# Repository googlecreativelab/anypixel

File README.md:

[AnyPixel.js](http://googlecreativelab.github.io/anypixel) is an open-source software and hardware library that makes it possible to use the web to create big, unusual, interactive displays. Anyone can fork the code and the schematics to create their own display at any scale.

The first display using this platform is in the 8th Avenue lobby at the Google NYC office. To create this installation, we used 5880 off-the-shelf arcade buttons with LEDs inside them as our pixels. AnyPixel.js’ straightforward hardware/software framework makes it easy to build any display where each pixel is an interactive element.

## What You'll Find
- **/hardware** - EAGLE schematics, board layouts, CAD files, wiring diagrams, and blueprints.
- **/firmware** - microcontroller code, written for the STM32 family of devices.
- **/backend** - node.js and chrome applications for communicating with the hardware.
- **/frontend** - the app framework, an in-browser previewer, and 12 example apps written by Googlers and friends worldwide.
- **/rpi-example** - a simple starter example connecting a Raspberry Pi with AnyPixel to a single button for round trip communication.

## Getting Started

### Check out the examples 
We've included 12 example apps written by Googlers and friends for the 8th Avenue lobby display in NYC. To check them out, install the [previewer](https://github.com/googlecreativelab/anypixel/tree/master/frontend/previewer) and run one of the [examples](https://github.com/googlecreativelab/anypixel/tree/master/frontend/examples).

### Build your own app 
Building your own app is easy with the Anypixel framework. To get started, check out the [framework documentation](https://github.com/googlecreativelab/anypixel/tree/master/frontend/framework) and the [example app](https://github.com/googlecreativelab/anypixel/tree/master/frontend/examples/getting-started):

```js
var anypixel = require('anypixel'); 
var ctx = anypixel.canvas.getContext2D();

var colors = ['#F00', '#0F0', '#00F'];

/**  
 * Listen for onButtonDown events and draw a 2x2 rectangle at the event site
 */
document.addEventListener('onButtonDown', function(event) {   
	ctx.fillStyle = colors[Math.floor(Math.random() * colors.length)];
	ctx.fillRect(event.detail.x - 1, event.detail.y - 1, 2, 2);
}); 
```

## Contributors
- [Jeremy Abel](https://github.com/jeremyabel)
- [Kyle Phillips](https://github.com/hapticdata)
- [Nick Fox-Gieg](https://github.com/n1ckfg)
- [Jeramy Morrill](https://github.com/theceremony)
- [Manny Tan](https://github.com/mannytan)
- [Felix Woitzel](https://github.com/flexi23)
- [Anders Hoff](https://github.com/inconvergent)
- [Dimitry Bentsionov](https://github.com/dimitry)
- [Nick Stahlnecker](https://github.com/Stahlneckr)
- [Nick Jonas](https://github.com/nick-jonas)
- [Patrick Miller](https://github.com/patrickdmiller)

## Note
Third party directories may have different (non-Apache 2.0) licenses.

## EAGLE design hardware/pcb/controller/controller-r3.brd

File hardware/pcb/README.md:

# Electronics Overview

## Power

24v power is delivered from the power supply boxes to the LED boards through a 4A fuse. On each LED
board the 24v rail powers three identical 5v buck converters (or alternatively a single 1/4 brick
supply with the three 5v rails bridged together) which provide power to the LEDs and is further
stepped down to 3.3v to power the microcontrollers.  There is also a power supply that steps the 24v
down to 12v to power the cooling fan. The 24v rail is also connected to the RJ12 connection which
goes to the IP controller.

The IP controller has a diode ORing arrangement, accepting power from any of the 4 LED boards and/or
an additional external supply via a barrel connector. There are two switching supplies on the IP
controller board, one with a 3.3v output to power all the onboard electronics, and a 5v output
device for powering accessories through a 2 pin header.

## Data Flow

The IP controller board contains a 3 port 100Mbit Ethernet switch with two ports exposed as RJ45
connectors which allows for daisy chaining boards together eliminating the need for long cable runs
back to a single large switch. The third port of this switch is connected to the STM32F407
microcontroller on the IP controller which takes in packets containing data for a complete 14x14
button panel. The firmware divides this data into 4 smaller packets and send these to the 4
connected 7x7 LED boards.

Communication to the LED boards is over asynchronous serial with a baud rate of 1Mbit.  There are 5
STM32F030 microcontrollers on each LED board that each control 9 or 10 RGB LEDs and have the same
number of thermistors and switches as input.  The thermistors are used to report the temperature of
each LED, and the switch is used for user input. The microcontrollers are connected in a chain, with
the TX from the IP controller connected to the first microcontroller's RX, and then the first
microcontroller's TX to the second microcontroller's RX and so on until the 5th microcontroller's TX
connects back to the IP controller's RX.  This configuration and the firmware make the LED board
behave like a large shift register, with each processor gathering its input and replacing it with
its output in the appropriate location in each packet based on its address as the stream of data is
shifted through it.  The packets are delimited by an idle state on the serial line (no signal edges
occur in the time it takes to transmit a complete byte, or about 10 microseconds).

The interface from the STM32F030 microcontrollers to the two TLC59401 LED drivers it controls is
like a shift register as well.  The two TLC59401 chips are connected in series.  There are
additional connections to the TLC59401 to facilitate the PWM signal generation, these include a
grayscale clock and a blanking signal.

## LED drive

The TLC59401 chip is a 16 channel constant current supply PWM controlled LED driver.  The device has
a global reference resistor to set the maximum channel current.  Each channel then has an analog dot
correct circuit which controls the current reference in 64 steps.  This dot correction feature is
used for rough calibration and is not changed during operation.  The global reference combined with
the dot correction circuit provide for a constant current output to drive the LEDs.

The TLC59401 also has PWM to toggle the constant current outputs on and off with a programmable duty
cycle. This is a 12-bit PWM system yielding 4096 discrete intensities for the output on top of the
5-bit/64 value dot correction values, which provides a 17-bit range for the system.  The firmware
implements a lookup table for converting from the typical 8-bits per channel input media to the
12-bit PWM values. Due to memory constrains the lookup table has only 65 entries and uses linear
interpolation to map the complete 256-value/8-bit input range to appropriate output values.

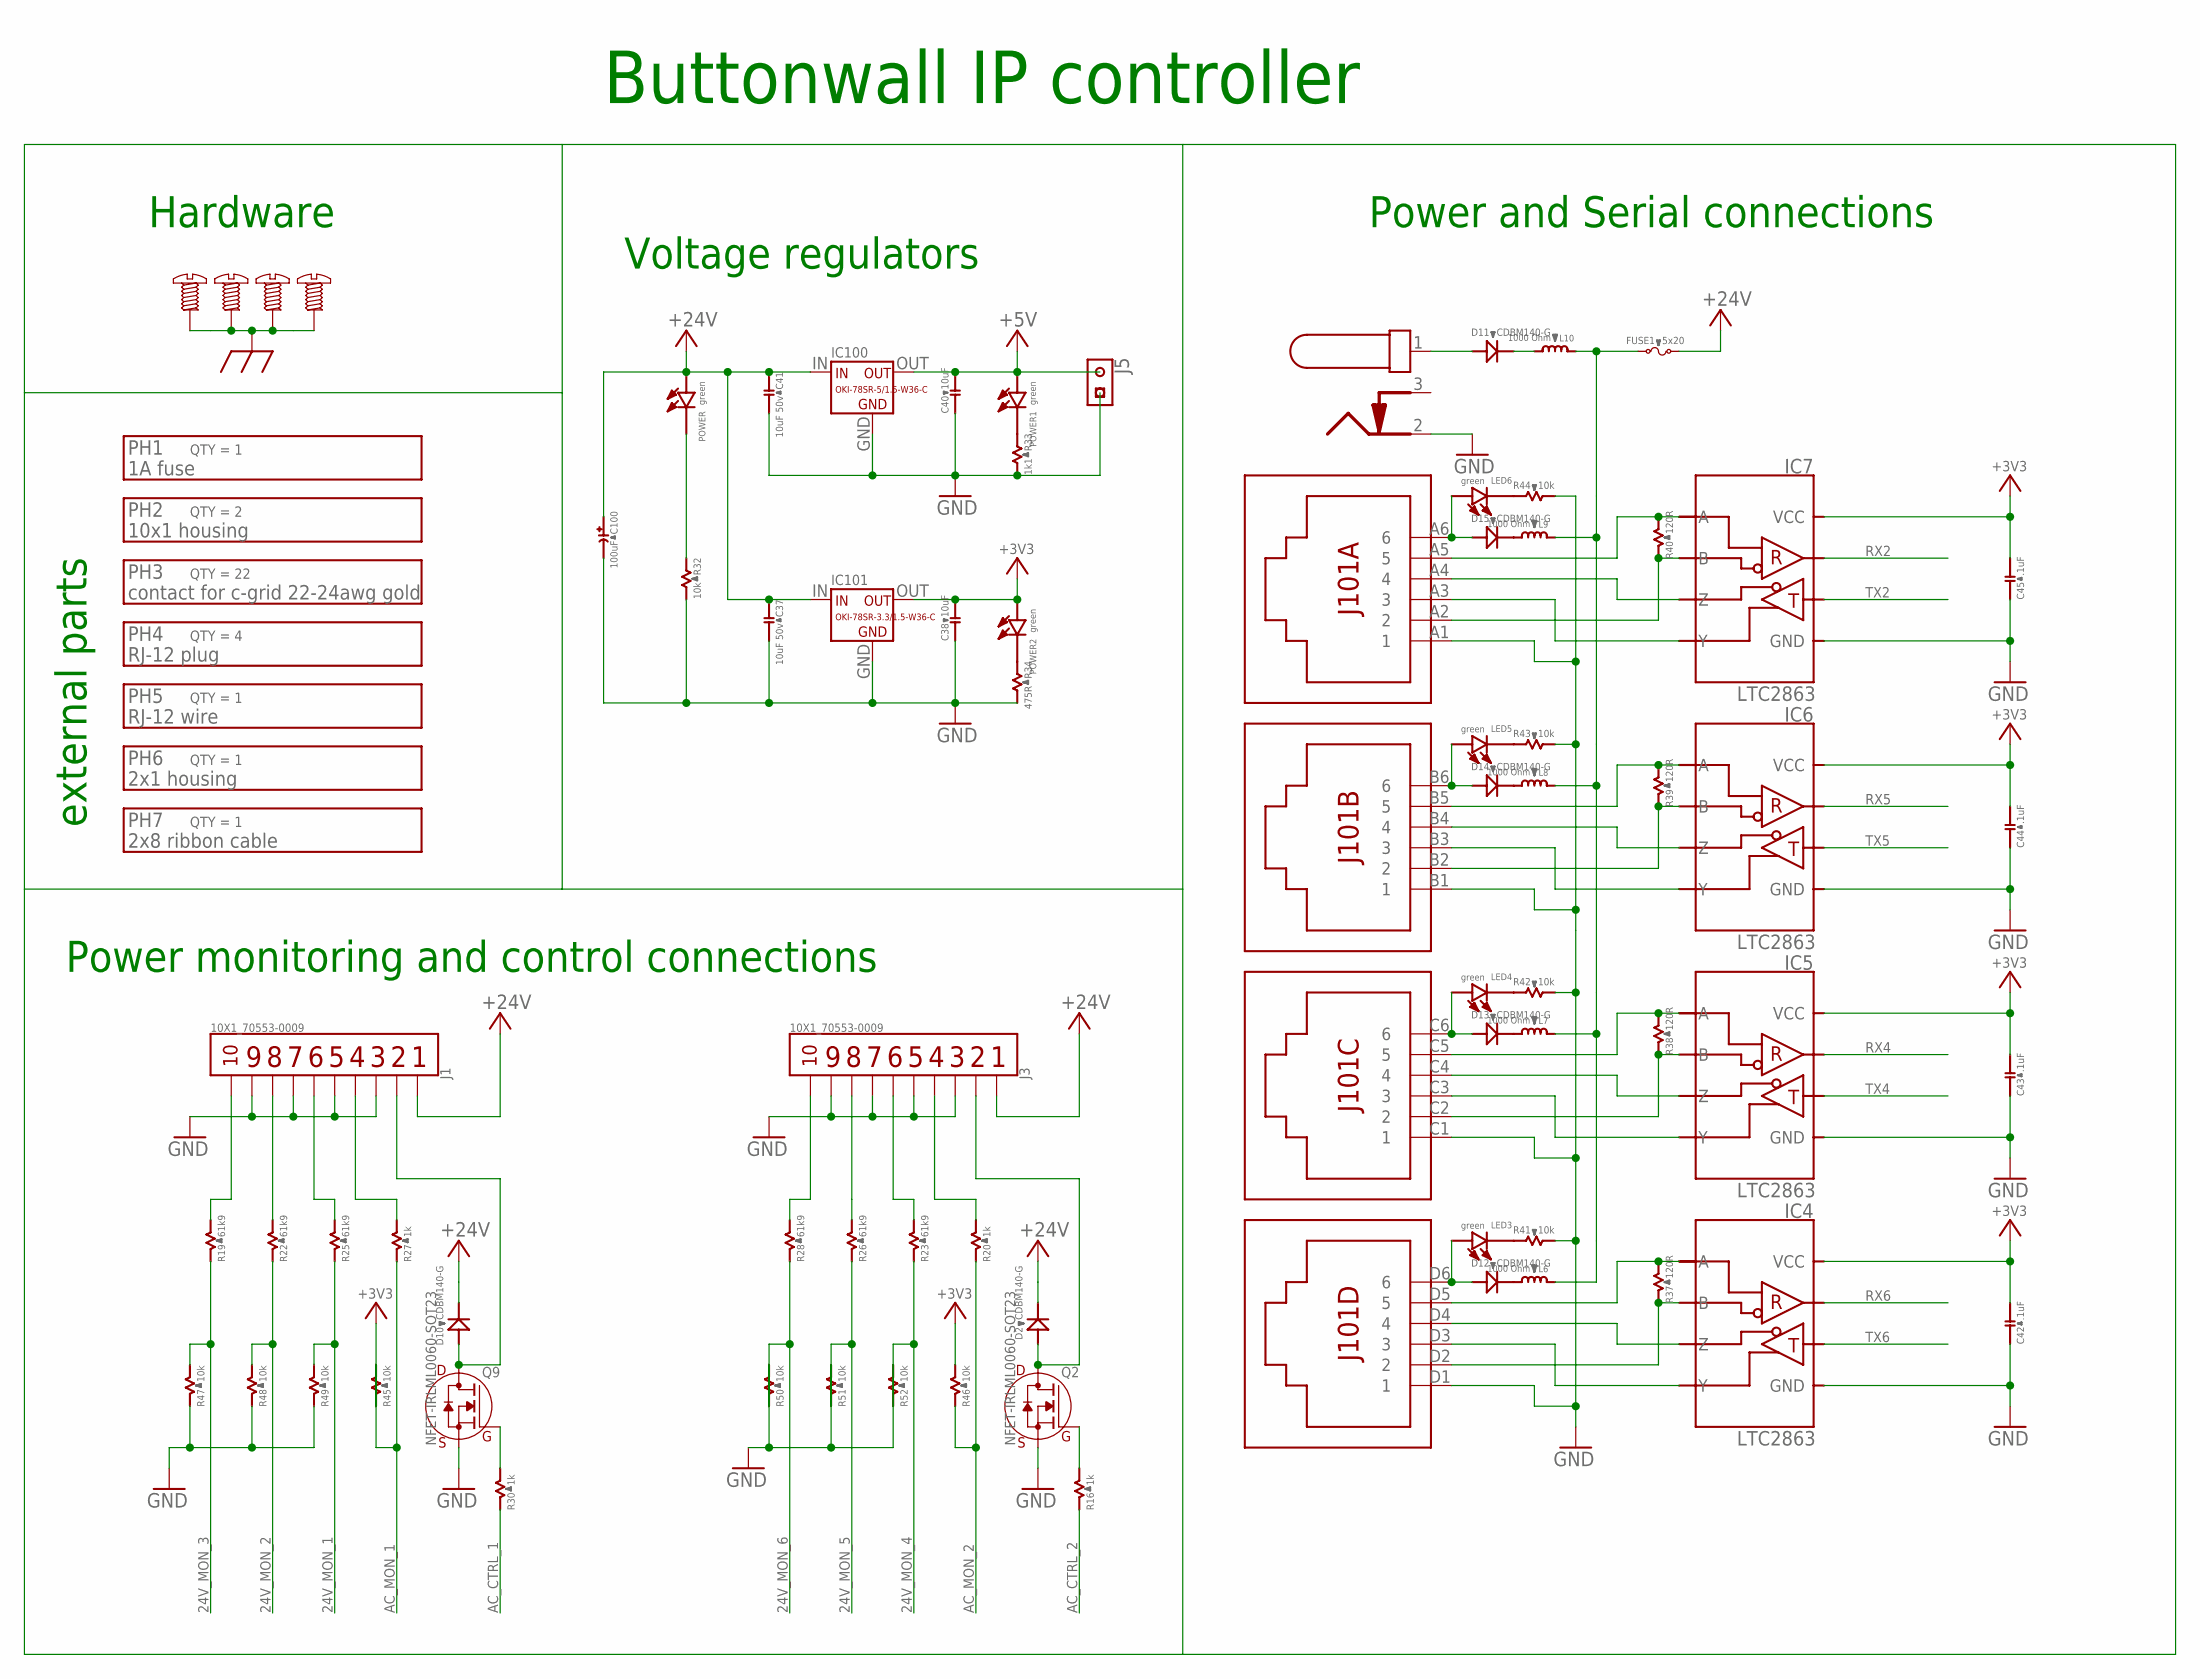
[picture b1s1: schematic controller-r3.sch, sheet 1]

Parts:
C37, C41: 10uF 50v; C1206B; PARTNO CL31A106KBHNNNE
C38, C40: 10uF; C0603B; PARTNO C1608X6S1A106M080AC
C42, C43, C44, C45: .1uF; C0603B; PARTNO CGA3E2X7R1H104K080AA
C100: 100uF; E3,5-8; PARTNO EEU-FM1H101
D2, D10, D11, D12, D13, D14, D15: CDBM140-G; SOD-123; PARTNO CDBM140-G
FUSE1: 5x20; 649; PARTNO 64900001039
IC4, IC5, IC6, IC7: LTC2863; SO08; PARTNO LTC2863IS8-1#PBF
IC100: OKI-78SR-5/1.5-W36-C; OKI-78SR-V; PARTNO OKI-78SR-5/1.5-W36-C
IC101: OKI-78SR-3.3/1.5-W36-C; OKI-78SR-V; PARTNO OKI-78SR-3.3/1.5-W36-C
J1, J3: 10X1_70553-0009; MOLEX_70553-(10); PARTNO 0705530009
J5: 1X2_70543; MOLEX_70543-0001; PARTNO 0705430001
J100: PJ-102AH; PJ-102(DC_JACK); PARTNO PJ-102AH
J101: RJ12-QUAD; SS-666604-NF; PARTNO SS-666604-NF
L6, L7, L8, L9, L10: 1000 Ohm; R0603B; PARTNO MMZ1608R102A
LED3, LED4, LED5, LED6: green; CHIPLED_0603; PARTNO LTST-C190KGKT
POWER, POWER1, POWER2: green; CHIPLED_0603; PARTNO LTST-C190KGKT
Q2, Q9: NFET-IRLML0060-SOT23; SOT-23; PARTNO IRLML0060TRPBF
R16, R20, R27, R30: 1k; R0603B; PARTNO CRCW06031K00FKEA
R19, R22, R23, R25, R26, R28: 61k9; R0603B; PARTNO CRCW060361K9FKEA
R32, R41, R42, R43, R44, R45, R46, R47, R48, R49, R50, R51, R52: 10k; R0603B; PARTNO CRCW060310K0FKEA
R33: 1k1; R0603B; PARTNO CRCW06031K10FKEA
R34: 475R; R0603B; PARTNO CRCW0603475RFKEA
R37, R38, R39, R40: 120R; R1206B; PARTNO CRCW1206120RFKEA
SCREW1, SCREW2, SCREW3, SCREW4: SCREW-632-0-PSHP; SMTPR-6-1

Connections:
24V_MON_1: R25.1, R49.2; also elsewhere on the board
24V_MON_2: R22.1, R48.2; also elsewhere on the board
24V_MON_3: R19.1, R47.2; also elsewhere on the board
24V_MON_4: R23.1, R52.1; also elsewhere on the board
24V_MON_5: R26.1, R51.1; also elsewhere on the board
24V_MON_6: R28.1, R50.1; also elsewhere on the board
+3V3: C38.2, C42.2, C43.2, C44.2, C45.2, IC4.1 (VCC), IC5.1 (VCC), IC6.1 (VCC), IC7.1 (VCC), IC101.OUT, POWER2.A (ANODE), R45.1, R46.2; also elsewhere on the board
+5V: C40.2, IC100.OUT, J5.2, POWER1.A (ANODE)
+24V: C37.1, C41.1, C100.+, D2.C (K), D10.C (K), FUSE1.2, IC100.IN, IC101.IN, J1.1, J3.1, POWER.A (ANODE)
AC_CTRL_1: R30.1; also elsewhere on the board
AC_CTRL_2: R16.1; also elsewhere on the board
AC_MON_1: R27.1, R45.2; also elsewhere on the board
AC_MON_2: R20.1, R46.1; also elsewhere on the board
CHASSIS: SCREW1.P$1, SCREW2.P$1, SCREW3.P$1, SCREW4.P$1; also elsewhere on the board
GND: C37.2, C38.1, C40.1, C41.2, C42.1, C43.1, C44.1, C45.1, C100.-, IC4.4 (GND), IC5.4 (GND), IC6.4 (GND), IC7.4 (GND), IC100.GND, IC101.GND, J1.3, J1.5, J1.7, J1.9, J3.3, J3.5, J3.7, J3.9, J5.1, J100.2 (SLEEVE), J101.A1 (1), J101.B1 (1), J101.C1 (1), J101.D1 (1), Q2.2 (S), Q9.2 (S), R32.2, R33.2, R34.2, R41.2, R42.2, R43.2, R44.2, R47.1, R48.1, R49.1, R50.2, R51.2, R52.2; also elsewhere on the board
unnamed: IC7.7 (B), J101.A2 (2), R40.1
unnamed: POWER1.C (CATHODE), R33.1
unnamed: IC7.8 (A), J101.A5 (5), R40.2
unnamed: D15.C (K), L9.2
unnamed: POWER.C (CATHODE), R32.1
unnamed: IC7.5 (Y), J101.A3 (3)
unnamed: IC7.6 (Z), J101.A4 (4)
unnamed: IC6.7 (B), J101.B2 (2), R39.1
unnamed: IC6.8 (A), J101.B5 (5), R39.2
unnamed: D15.A, J101.A6 (6), LED6.A (ANODE)
unnamed: IC6.5 (Y), J101.B3 (3)
unnamed: IC6.6 (Z), J101.B4 (4)
unnamed: IC5.7 (B), J101.C2 (2), R38.1
unnamed: IC5.8 (A), J101.C5 (5), R38.2
unnamed: D14.C (K), L8.2
unnamed: IC5.5 (Y), J101.C3 (3)
unnamed: IC5.6 (Z), J101.C4 (4)
unnamed: IC4.7 (B), J101.D2 (2), R37.1
unnamed: IC4.8 (A), J101.D5 (5), R37.2
unnamed: D14.A, J101.B6 (6), LED5.A (ANODE)
unnamed: IC4.5 (Y), J101.D3 (3)
unnamed: IC4.6 (Z), J101.D4 (4)
unnamed: J1.4, R27.2
unnamed: J1.10, R19.2
unnamed: J1.8, R22.2
unnamed: J1.6, R25.2
unnamed: D10.A, J1.2, Q9.3 (D)
unnamed: Q9.1 (G), R30.2
unnamed: D13.C (K), L7.2
unnamed: D13.A, J101.C6 (6), LED4.A (ANODE)
unnamed: D12.C (K), L6.2
unnamed: D12.A, J101.D6 (6), LED3.A (ANODE)
unnamed: D11.C (K), L10.2
unnamed: D11.A, J100.1 (CENTER)
unnamed: J3.10, R28.2
unnamed: J3.8, R26.2
unnamed: J3.6, R23.2
unnamed: J3.4, R20.2
unnamed: D2.A, J3.2, Q2.3 (D)
unnamed: Q2.1 (G), R16.2
unnamed: POWER2.C (CATHODE), R34.1
unnamed: FUSE1.1, L6.1, L7.1, L8.1, L9.1, L10.1
unnamed: LED5.C (CATHODE), R43.1
unnamed: LED6.C (CATHODE), R44.1
unnamed: LED4.C (CATHODE), R42.1
unnamed: LED3.C (CATHODE), R41.1
RX2: IC7.2 (RO); also elsewhere on the board
RX4: IC5.2 (RO); also elsewhere on the board
RX5: IC6.2 (RO); also elsewhere on the board
RX6: IC4.2 (RO); also elsewhere on the board
TX2: IC7.3 (DI); also elsewhere on the board
TX4: IC5.3 (DI); also elsewhere on the board
TX5: IC6.3 (DI); also elsewhere on the board
TX6: IC4.3 (DI); also elsewhere on the board

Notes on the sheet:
Buttonwall IP controller
Hardware
Voltage regulators
Power and Serial connections
external parts
Power monitoring and control connections

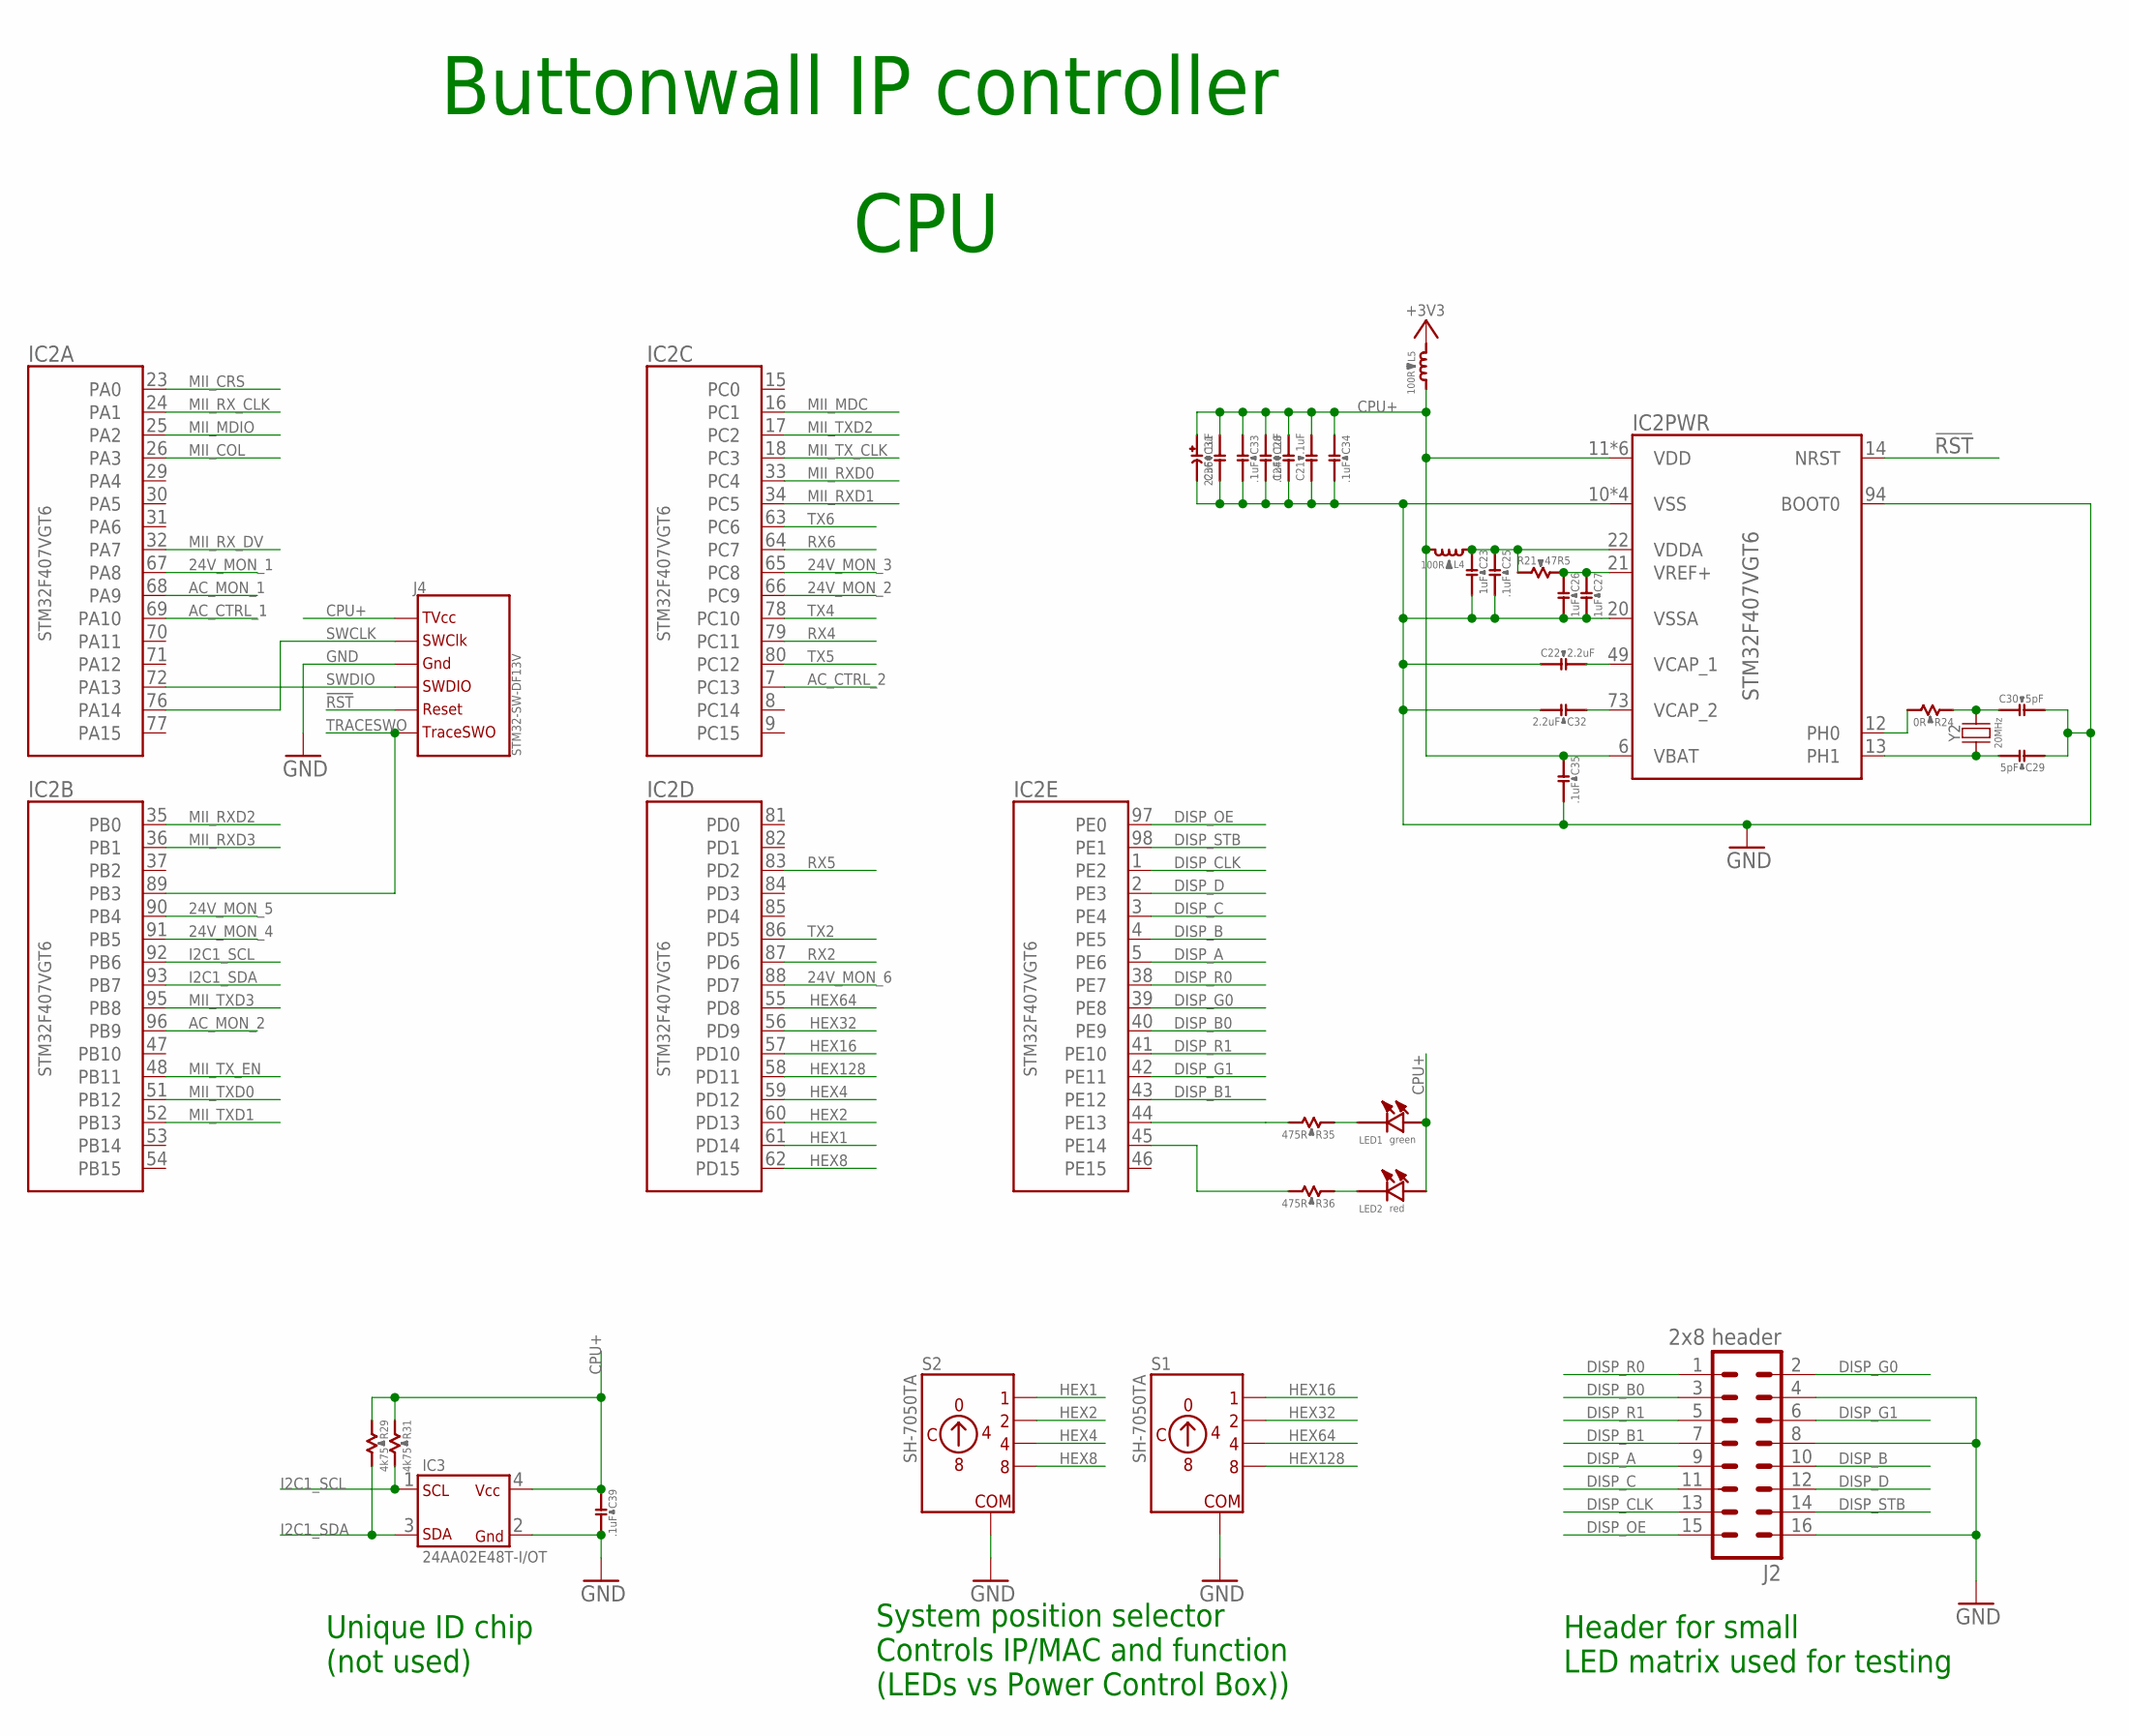
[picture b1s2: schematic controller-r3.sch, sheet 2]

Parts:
C21, C24, C25, C27, C28, C33, C34, C35, C36, C39: .1uF; C0603B; PARTNO CGA3E2X7R1H104K080AA
C22, C32: 2.2uF; C0603B; PARTNO C1608X5R1V225K080AC
C23, C26: 1uF; C0603B; PARTNO CGA3E3X5R1H105K080AB
C29, C30: 5pF; C0603B; PARTNO CGA3E2C0G1H050C080AA
C31: 22uF; B/3528-21R; PARTNO 293D226X96R3B2TE3
IC2: STM32F407VGT6; LQFP-100; PARTNO STM32F407VGT6
IC3: 24AA02E48T-I/OT; SOT-23-5; PARTNO 24AA02E48T-I/OT
J2: 2x8 header; ML16; PARTNO SBH11-PBPC-D08-ST-BK
J4: STM32-SW-DF13V; DF13-6P-1.25V; PARTNO DF13C-6P-1.25V(20)
L4, L5: 100R; R0603B; PARTNO MPZ1608S101A
LED1: green; CHIPLED_0603; PARTNO LTST-C190KGKT
LED2: red; CHIPLED_0603; PARTNO LTST-C190KRKT
R21: 47R5; R0603B; PARTNO CRCW060347R5FKEA
R24: 0R; R0603B; PARTNO CRCW06030000Z0EA
R29, R31: 4k75; R0603B; PARTNO CRCW06034K75FKEA
R35, R36: 475R; R0603B; PARTNO CRCW0603475RFKEA
S1, S2: SH-7050TA; PARTNO SH-7050TA
Y2: 20MHz; 5X3.2; PARTNO 7A-20.000MAHE-T

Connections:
24V_MON_1: IC2.67 (PA8); also elsewhere on the board
24V_MON_2: IC2.66 (PC9); also elsewhere on the board
24V_MON_3: IC2.65 (PC8); also elsewhere on the board
24V_MON_4: IC2.91 (PB5); also elsewhere on the board
24V_MON_5: IC2.90 (PB4); also elsewhere on the board
24V_MON_6: IC2.88 (PD7); also elsewhere on the board
!RST: IC2.14 (NRST), J4.5 (RESET)
+3V3: L5.1; also elsewhere on the board
AC_CTRL_1: IC2.69 (PA10); also elsewhere on the board
AC_CTRL_2: IC2.7 (PC13); also elsewhere on the board
AC_MON_1: IC2.68 (PA9); also elsewhere on the board
AC_MON_2: IC2.96 (PB9); also elsewhere on the board
CPU+: C21.2, C24.2, C28.1, C31.+, C33.1, C34.1, C35.1, C36.2, C39.1, IC2.6 (VBAT), IC2.11 (VDD), IC2.19 (VDD), IC2.28 (VDD), IC2.50 (VDD), IC2.75 (VDD), IC2.100 (VDD), IC3.4 (VCC), J4.1 (TVCC), L4.2, L5.2, LED1.A (ANODE), LED2.A (ANODE), R29.1, R31.1
DISP_A: IC2.5 (PE6), J2.9
DISP_B: IC2.4 (PE5), J2.10
DISP_B0: IC2.40 (PE9), J2.3
DISP_B1: IC2.43 (PE12), J2.7
DISP_C: IC2.3 (PE4), J2.11
DISP_CLK: IC2.1 (PE2), J2.13
DISP_D: IC2.2 (PE3), J2.12
DISP_G0: IC2.39 (PE8), J2.2
DISP_G1: IC2.42 (PE11), J2.6
DISP_OE: IC2.97 (PE0), J2.15
DISP_R0: IC2.38 (PE7), J2.1
DISP_R1: IC2.41 (PE10), J2.5
DISP_STB: IC2.98 (PE1), J2.14
GND: C21.1, C22.1, C23.2, C24.1, C25.2, C26.2, C27.2, C28.2, C29.1, C30.2, C31.-, C32.2, C33.2, C34.2, C35.2, C36.1, C39.2, IC2.10 (VSS), IC2.20 (VSSA), IC2.27 (VSS), IC2.74 (VSS), IC2.94 (BOOT0), IC2.99 (VSS), IC3.2 (GND), J2.4, J2.8, J2.16, J4.3 (GND), S1.C (COM), S1.C@2 (COM), S2.C (COM), S2.C@2 (COM); also elsewhere on the board
HEX1: IC2.61 (PD14), S2.1
HEX2: IC2.60 (PD13), S2.2
HEX4: IC2.59 (PD12), S2.4
HEX8: IC2.62 (PD15), S2.8
HEX16: IC2.57 (PD10), S1.1
HEX32: IC2.56 (PD9), S1.2
HEX64: IC2.55 (PD8), S1.4
HEX128: IC2.58 (PD11), S1.8
I2C1_SCL: IC2.92 (PB6), IC3.1 (SCL), R31.2
I2C1_SDA: IC2.93 (PB7), IC3.3 (SDA), R29.2
MII_COL: IC2.26 (PA3); also elsewhere on the board
MII_CRS: IC2.23 (PA0); also elsewhere on the board
MII_MDC: IC2.16 (PC1); also elsewhere on the board
MII_MDIO: IC2.25 (PA2); also elsewhere on the board
MII_RXD0: IC2.33 (PC4); also elsewhere on the board
MII_RXD1: IC2.34 (PC5); also elsewhere on the board
MII_RXD2: IC2.35 (PB0); also elsewhere on the board
MII_RXD3: IC2.36 (PB1); also elsewhere on the board
MII_RX_CLK: IC2.24 (PA1); also elsewhere on the board
MII_RX_DV: IC2.32 (PA7); also elsewhere on the board
MII_TXD0: IC2.51 (PB12); also elsewhere on the board
MII_TXD1: IC2.52 (PB13); also elsewhere on the board
MII_TXD2: IC2.17 (PC2); also elsewhere on the board
MII_TXD3: IC2.95 (PB8); also elsewhere on the board
MII_TX_CLK: IC2.18 (PC3); also elsewhere on the board
MII_TX_EN: IC2.48 (PB11); also elsewhere on the board
unnamed: IC2.12 (PH0), R24.2
unnamed: C29.2, IC2.13 (PH1), Y2.1
unnamed: C30.1, R24.1, Y2.2
unnamed: C22.2, IC2.49 (VCAP_1)
unnamed: C32.1, IC2.73 (VCAP_2)
unnamed: C23.1, C25.1, IC2.22 (VDDA), L4.1, R21.1
unnamed: C26.1, C27.1, IC2.21 (VREF+), R21.2
unnamed: LED1.C (CATHODE), R35.1
unnamed: LED2.C (CATHODE), R36.1
unnamed: IC2.45 (PE14), R36.2
unnamed: IC2.44 (PE13), R35.2
RX2: IC2.87 (PD6); also elsewhere on the board
RX4: IC2.79 (PC11); also elsewhere on the board
RX5: IC2.83 (PD2); also elsewhere on the board
RX6: IC2.64 (PC7); also elsewhere on the board
SWCLK: IC2.76 (PA14), J4.2 (SWCLK)
SWDIO: IC2.72 (PA13), J4.4 (SWDIO)
TRACESWO: IC2.89 (PB3), J4.6 (TRACESWO)
TX2: IC2.86 (PD5); also elsewhere on the board
TX4: IC2.78 (PC10); also elsewhere on the board
TX5: IC2.80 (PC12); also elsewhere on the board
TX6: IC2.63 (PC6); also elsewhere on the board

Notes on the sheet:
CPU
Buttonwall IP controller
Unique ID chip (not used)
System position selector Controls IP/MAC and function (LEDs vs Power Control Box))
Header for small LED matrix used for testing

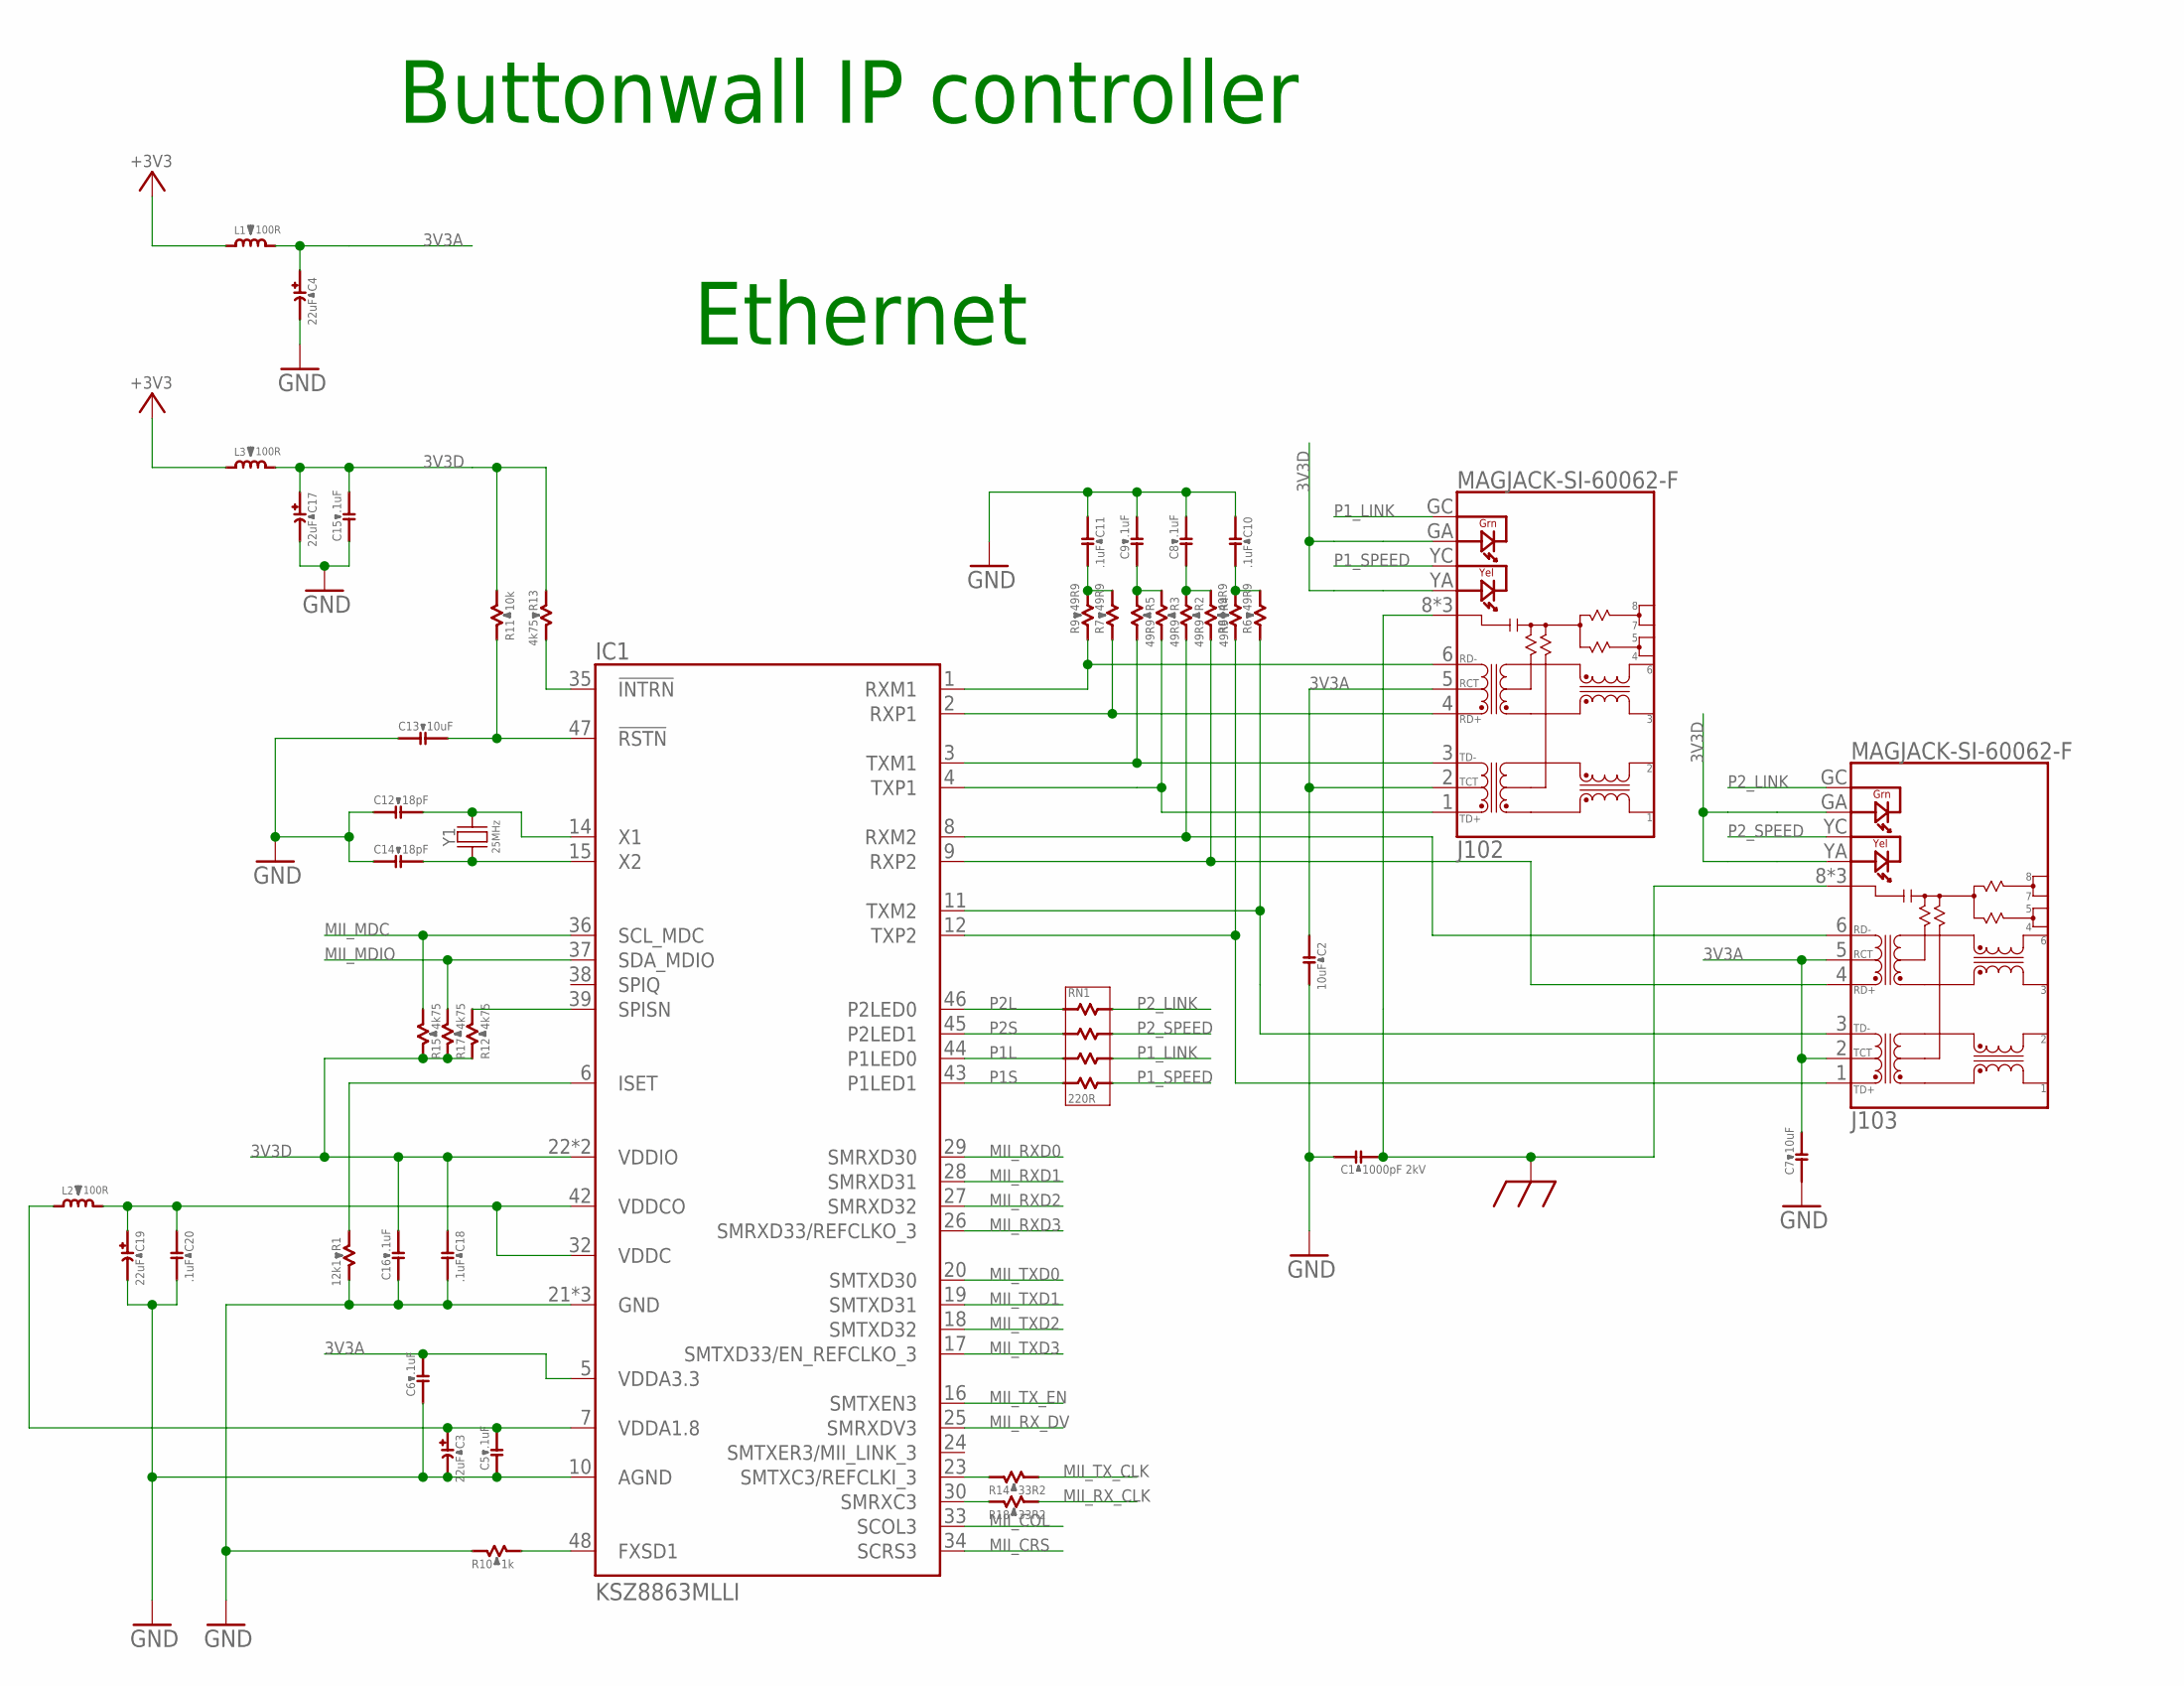
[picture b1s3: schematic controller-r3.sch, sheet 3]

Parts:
C1: 1000pF 2kV; C1206B; PARTNO 202R18W102KV4E
C2, C7, C13: 10uF; C0603B; PARTNO C1608X6S1A106M080AC
C3, C4, C17, C19: 22uF; B/3528-21R; PARTNO 293D226X96R3B2TE3
C5, C6, C8, C9, C10, C11, C15, C16, C18, C20: .1uF; C0603B; PARTNO CGA3E2X7R1H104K080AA
C12, C14: 18pF; C0603B; PARTNO CGA3E2C0G1H180J080AA
IC1: KSZ8863MLLI; TQFP48; PARTNO KSZ8863MLLI
J102, J103: MAGJACK-SI-60062-F; SI-60062-F; PARTNO SI-60062-F
L1, L2, L3: 100R; R0603B; PARTNO MPZ1608S101A
R1: 12k1; R0603B; PARTNO CRCW060312K1FKEA
R2, R3, R4, R5, R6, R7, R8, R9: 49R9; R0603B; PARTNO CRCW060349R9FKEA
R10: 1k; R0603B; PARTNO CRCW06031K00FKEA
R11: 10k; R0603B; PARTNO CRCW060310K0FKEA
R12, R13, R15, R17: 4k75; R0603B; PARTNO CRCW06034K75FKEA
R14, R18: 33R2; R0603B; PARTNO CRCW060333R2FKEA
RN1: 220R; CTS_742-4; PARTNO 742C083221JP
Y1: 25MHz; 5X3.2; PARTNO 7A-25.000MAHE-T

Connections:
3V3A: C2.1, C4.+, C6.2, C7.2, IC1.5 (VDDA3.3), J102.2 (TCT), J102.5 (RCT), J103.2 (TCT), J103.5 (RCT), L1.2
3V3D: C15.2, C16.2, C17.+, C18.1, IC1.22 (VDDIO), IC1.40 (VDDIO), J102.GA, J102.YA, J103.GA, J103.YA, L3.2, R11.2, R12.1, R13.1, R15.1, R17.1
+3V3: L1.1, L3.1; also elsewhere on the board
CHASSIS: C1.2, J102.8 (CHASSIS), J102.P$1 (CHASSIS), J102.P$2 (CHASSIS), J103.8 (CHASSIS), J103.P$1 (CHASSIS), J103.P$2 (CHASSIS); also elsewhere on the board
GND: C1.1, C2.2, C3.-, C4.-, C5.1, C6.1, C7.1, C8.2, C9.2, C10.1, C11.1, C12.1, C13.1, C14.1, C15.1, C16.1, C17.-, C18.2, C19.-, C20.2, IC1.10 (AGND), IC1.21 (GND), IC1.31 (GND), IC1.41 (GND), R1.2, R10.1; also elsewhere on the board
MII_COL: IC1.33 (SCOL3); also elsewhere on the board
MII_CRS: IC1.34 (SCRS3); also elsewhere on the board
MII_MDC: IC1.36 (SCL_MDC), R15.2; also elsewhere on the board
MII_MDIO: IC1.37 (SDA_MDIO), R17.2; also elsewhere on the board
MII_RXD0: IC1.29 (SMRXD30); also elsewhere on the board
MII_RXD1: IC1.28 (SMRXD31); also elsewhere on the board
MII_RXD2: IC1.27 (SMRXD32); also elsewhere on the board
MII_RXD3: IC1.26 (SMRXD33/REFCLKO_3); also elsewhere on the board
MII_RX_CLK: R18.2; also elsewhere on the board
MII_RX_DV: IC1.25 (SMRXDV3); also elsewhere on the board
MII_TXD0: IC1.20 (SMTXD30); also elsewhere on the board
MII_TXD1: IC1.19 (SMTXD31); also elsewhere on the board
MII_TXD2: IC1.18 (SMTXD32); also elsewhere on the board
MII_TXD3: IC1.17 (SMTXD33/EN_REFCLKO_3); also elsewhere on the board
MII_TX_CLK: R14.2; also elsewhere on the board
MII_TX_EN: IC1.16 (SMTXEN3); also elsewhere on the board
unnamed: C11.2, R7.2, R9.2
unnamed: C9.1, R3.1, R5.1
unnamed: C8.1, R2.1, R4.1
unnamed: C10.2, R6.2, R8.2
unnamed: IC1.30 (SMRXC3), R18.1
unnamed: IC1.1 (RXM1), J102.6 (RD-), R9.1
unnamed: IC1.2 (RXP1), J102.4 (RD+), R7.1
unnamed: IC1.3 (TXM1), J102.3 (TD-), R5.2
unnamed: IC1.8 (RXM2), J103.6 (RD-), R2.2
unnamed: IC1.9 (RXP2), J103.4 (RD+), R4.2
unnamed: IC1.11 (TXM2), J103.3 (TD-), R6.1
unnamed: IC1.12 (TXP2), J103.1 (TD+), R8.1
unnamed: IC1.23 (SMTXC3/REFCLKI_3), R14.1
unnamed: C14.2, IC1.15 (X2), Y1.1
unnamed: C12.2, IC1.14 (X1), Y1.2
unnamed: IC1.35 (!INTRN), R13.2
unnamed: C13.2, IC1.47 (!RSTN), R11.1
unnamed: C3.+, C5.2, IC1.7 (VDDA1.8), L2.1
unnamed: IC1.48 (FXSD1), R10.2
unnamed: IC1.6 (ISET), R1.1
unnamed: IC1.39 (SPISN), R12.2
unnamed: IC1.4 (TXP1), J102.1 (TD+), R3.2
P1L: IC1.44 (P1LED0), RN1.C1
P1S: IC1.43 (P1LED1), RN1.D1
P1_LINK: J102.GC, RN1.C2
P1_SPEED: J102.YC, RN1.D2
P2L: IC1.46 (P2LED0), RN1.A1
P2S: IC1.45 (P2LED1), RN1.B1
P2_LINK: J103.GC, RN1.A2
P2_SPEED: J103.YC, RN1.B2
VDDC: C19.+, C20.1, IC1.32 (VDDC), IC1.42 (VDDCO), L2.2

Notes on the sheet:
Ethernet
Buttonwall IP controller

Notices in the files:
firmware/display/src/project_config.c:
Copyright 2016 Google Inc. All Rights Reserved.
Licensed under the Apache License, Version 2.0 (the "License");
